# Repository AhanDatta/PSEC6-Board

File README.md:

# PSEC6 Board
PCBs for the Kria K26-based test setup for PSEC6.

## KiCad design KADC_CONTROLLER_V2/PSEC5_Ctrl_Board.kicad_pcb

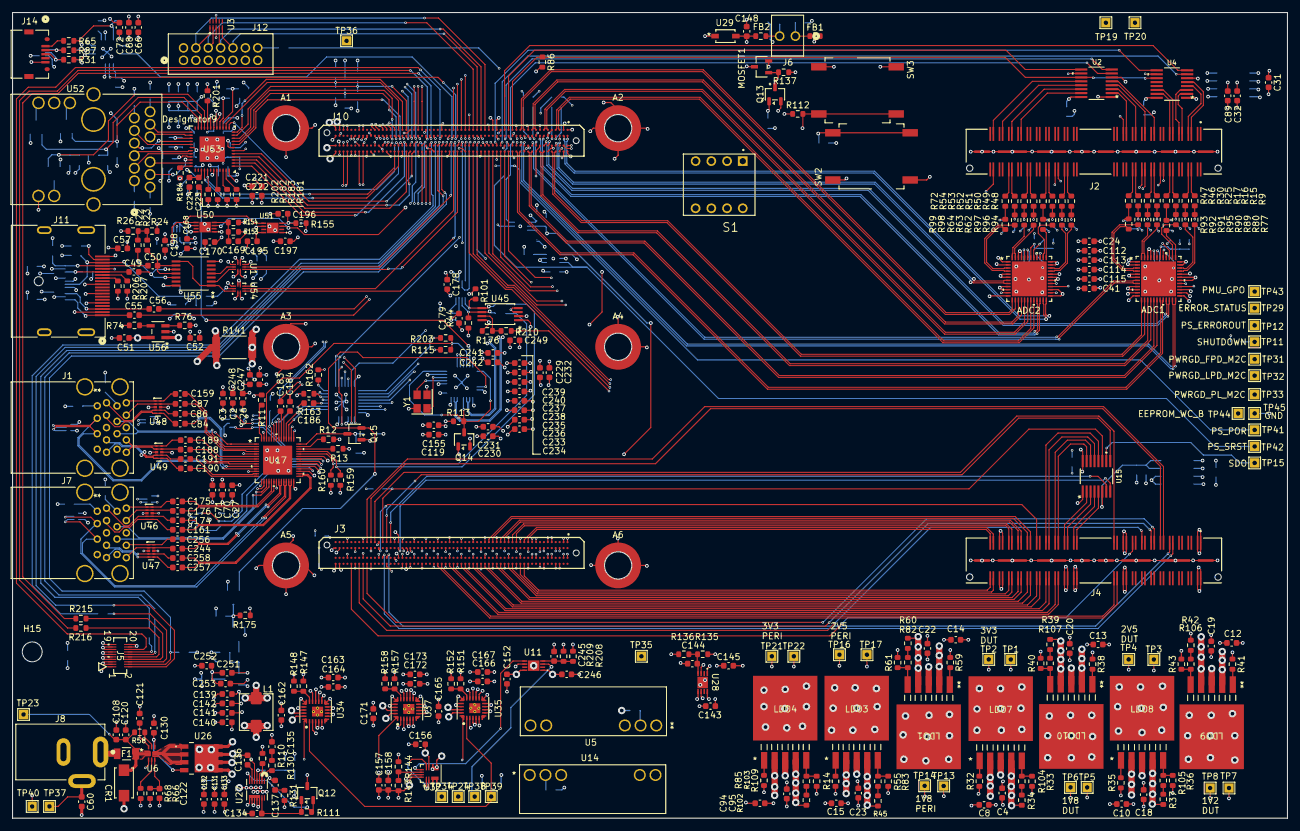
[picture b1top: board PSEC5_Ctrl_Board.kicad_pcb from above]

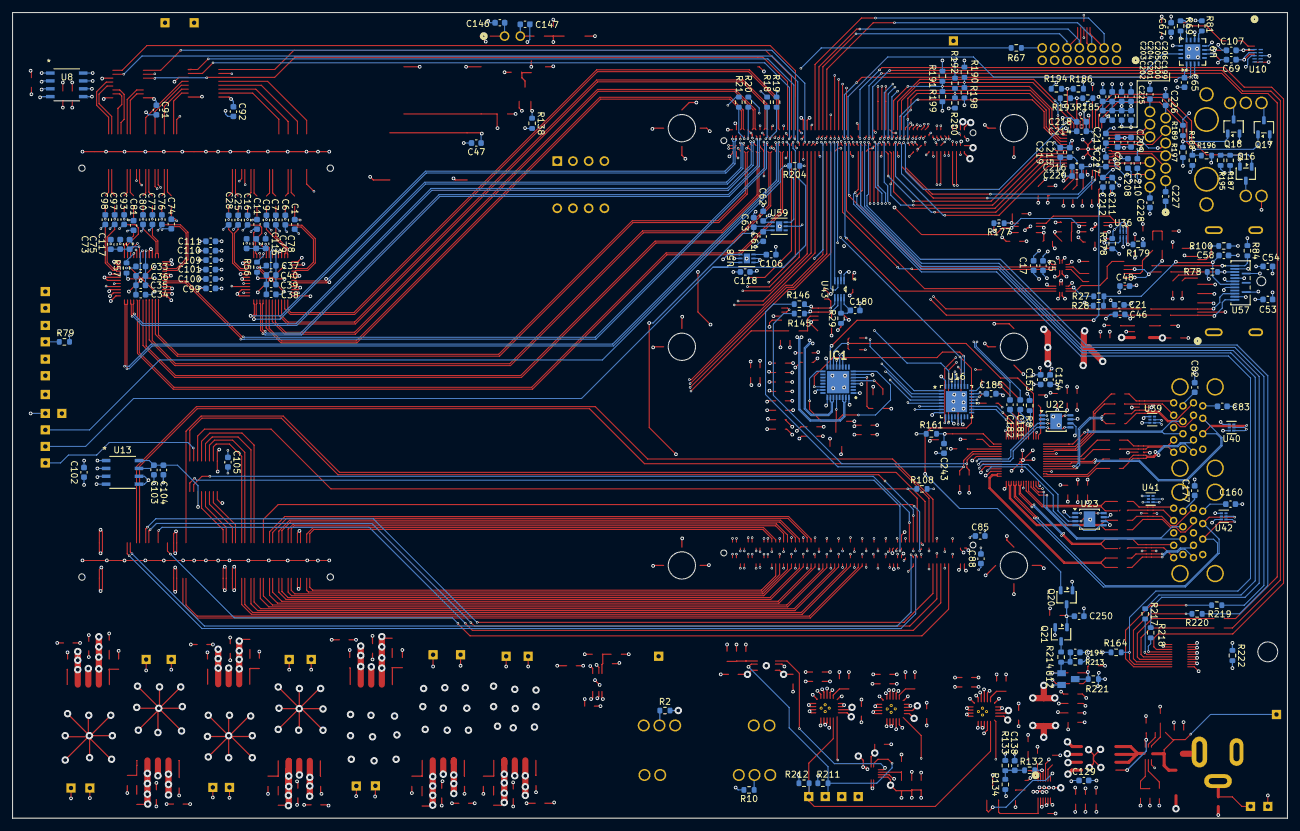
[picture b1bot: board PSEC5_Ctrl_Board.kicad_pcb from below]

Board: 10 copper layers, 206.0 x 130.2 mm, 544 parts (186 on the bottom side), 463 nets.

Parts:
A1, A2, A5, A6: 9774050960R; A_Wurth_WA-SMST_9774050960R_GND_ROUTE_FIX
A3, A4: DNP; A_Wurth_WA-SMST_9774050960R_GND_ROUTE_FIX
ADC1, ADC2: AD9228ABCPZ-65; CP_48_8_ADI
C1, C6, C7, C9, C11, C16, C25, C28, C74, C76, C77, C80, C81, C93, C97, C98, C122: 39p; C_0603_1608Metric
C2, C3, C27, C70, C71, C131, C132, C139, C140, C141, C142, C156, C157, C158, C162, C163, C164, C165, C166, C167, C171, C172, C173: 22u; C_0603_1608Metric
C4, C8, C10, C12, C13, C14, C15, C18, C19, C20, C22, C23, C82, C83, C94, C95, C108, C129, C143, C145, C152, C160, C168, C170, C177, C195, C197, C206, C211, C222, C246, C252: 10u; C_0603_1608Metric
C5, C17, C21, C24, C26, C31, C33, C34, C36, C37, C38, C40, C41, C46, C48, C49, C50, C51, C53, C54, C55, C56, C60, C75, C79, C84, C86, C87, C91, C92, C99, C100, C101, C102, C104, C105, C109, C110, C111, C112, C113, C114, C115, C119, C133, C135, C159, C161, C174, C175, C176, C178, C179, C181, C182, C183, C184, C185, C198, C199, C200, C201, C207, C208, C213, C214, C215, C216, C225, C226, C227, C228, C230, C232, C234, C236, C238, C240, C242, C248, C249, C253: 0.1u; C_0603_1608Metric
C32, C103: 1n; C_0603_1608Metric
C35, C39, C186: 2.2u; C_0603_1608Metric
C47, C61, C62, C65, C67, C72, C85, C88, C106, C118: 100n; C_0603_1608Metric
C52, C153, C154: 47u; C_0603_1608Metric
C57, C58: 10p; C_0603_1608Metric
C63: 10n; C_0603_1608Metric
C66, C68: 4.7u; C_0603_1608Metric
C69, C107: 47p; C_0603_1608Metric
C73, C78: 0.02u; C_0603_1608Metric
C89, C121, C130, C137, C146, C147: DNP; C_0603_1608Metric
C116, C117, C120, C134, C148, C155, C203, C204, C205, C209, C210, C217, C218, C219, C220, C229, C231, C233, C235, C237, C239, C241, C247: 1u; C_0603_1608Metric
C136: 22n; C_0603_1608Metric
C138: 56p; C_0603_1608Metric
C144, C169, C196, C245: 1000p; C_0603_1608Metric
C180: 100p; C_0603_1608Metric
C188, C189, C190, C191, C244, C256, C257, C258: 0.33u; C_0603_1608Metric
C194, C251: 0.47u; C_0603_1608Metric
C202, C212, C221: 0.01u; C_0603_1608Metric
C223, C224: 27p; C_0603_1608Metric
C243, C250: 22p; C_0603_1608Metric
CR1: SMAJ16A; DO214AC_LTF
F1: 0407004.WR; FUSE_407_LTF
FB1, FB2: 600R; R_0603_1608Metric
H15: MountingHole; MountingHole_3.2mm_M3_DIN965
IC1: SI5332BD08940-GM1; QFN50P500X500X90-33N-D
J1, J7: GSB311231HR; GSB311231HR_AMP
J2, J4: QSH-040-01-X-D-DP-A; SAMTEC_QSH-040-01-X-D-DP-A
J3: ADM6-60-01.5-L-4-2-A-TR_BOTTOM; SAMTEC_ADM6-60-01.5-L-4-2-A-TR
J5: DF40C-20DP-0.4V51; CONN20_6p6X2p9_hdr_HIR
J6: 22112022; CONN_A-6373-02A_MOL
J8: PJ-202BH; CUI_PJ-202BH
J10: ADM6-60-01.5-L-4-2-A-TR; SAMTEC_ADM6-60-01.5-L-4-2-A-TR
J11: 472720001; CONN_47272-0001_MOL_Shield_Fixed
J12: 878311420; CONN_87831-1420_MOL
J14: ZX62D-B-5P830; ZX62D-B-5P830_HIR
L1: 1.2u; L_Bourns_SRP5030T
LDO1, LDO3, LDO4, LDO7, LDO8, LDO9, LDO10: LP38501TS-ADJ/NOPB; TS5B
MOSFET1: NDS331N; SOT23_527AG_ONS
Q12, Q13, Q14, Q15, Q16, Q17, Q18, Q20, Q21: BSS806NEH6327XTSA1; SOT-23-3
R2: 4.42k; R_0603_1608Metric
R8, R67, R100, R130, R210, R221: 0R; R_0603_1608Metric
R9, R15, R16, R17, R25, R30, R46, R47, R48, R49, R50, R51, R52, R53, R54, R72: 33.2R; R_0603_1608Metric
R10, R44, R101, R201, R202: 2.21k; R_0603_1608Metric
R11: 12k; R_0603_1608Metric
R12, R13, R29, R157: 200k; R_0603_1608Metric
R14, R32, R33, R35, R36, R38, R40, R41, R43, R56, R57, R59, R61, R69, R74, R76, R79, R81, R83, R85, R109, R112, R136, R137, R138, R153, R154, R161, R163, R175, R177, R192, R204, R213: 10k; R_0603_1608Metric
R18, R19, R20, R21, R82, R86, R107, R108: 4.99k; R_0603_1608Metric
R22, R23: 49.9R; R_0603_1608Metric
R24: 1.5k; R_0603_1608Metric
R26, R198, R200: 2.49k; R_0603_1608Metric
R27, R62, R63, R64, R77, R80, R89, R90, R91, R92, R93, R94, R95, R96, R97, R98, R99: 10R; R_0603_1608Metric
R28, R78, R84, R110, R111, R147, R148, R151, R178, R179, R211, R212: 100k; R_0603_1608Metric
R31, R87: 27R; R_0603_1608Metric
R34, R102: 34k; R_0603_1608Metric
R37, R45, R133: 20k; R_0603_1608Metric
R39, R60: 14.7k; R_0603_1608Metric
R42: 6.8k; R_0603_1608Metric
R55, R105: 11.3k; R_0603_1608Metric
R58: 300k; R_0603_1608Metric
R65, R113, R164, R181, R182, R183: 4.7k; R_0603_1608Metric
R66: 274k; R_0603_1608Metric
R68: 422R; R_0603_1608Metric
R103, R104: 10.5k; R_0603_1608Metric
R106: 3.01k; R_0603_1608Metric
R115, R131, R145, R146, R159, R160, R185, R186, R187, R188, R189, R191, R193, R194, R195, R196, R197, R199, R203, R222: DNP; R_0603_1608Metric
R132, R176, R214: 1k; R_0603_1608Metric
R134: 2.7k; R_0603_1608Metric
R135: 56.2k; R_0603_1608Metric
R141: 0R; RES_HCJ2512_STP
R143: 80k; R_0603_1608Metric
R144: 25k; R_0603_1608Metric
R152: 49.9k; R_0603_1608Metric
R155: 40.2k; R_0603_1608Metric
R158: 44,2k; R_0603_1608Metric
R162: 8.06k; R_0603_1608Metric
R184: 11k; R_0603_1608Metric
R190: 5.76k; R_0603_1608Metric
R206, R207: 1M; R_0603_1608Metric
R208: 26.1k; R_0603_1608Metric
R209: 10.0k; R_0603_1608Metric
R215, R216, R217, R218, R219, R220: 30R; R_0603_1608Metric
S1: DS01C-254-S-04BE; SW_DS01C-254-S-04BE
SW2, SW3: SW_MEC_5G; SW_MEC_5GSH9
TP1, TP3, TP5, TP7, TP13, TP17, TP22, TP40: GND; TestPoint_THTPad_1.5x1.5mm_Drill0.7mm
TP2: 3V3_DUT; TestPoint_THTPad_1.5x1.5mm_Drill0.7mm
TP4: 2V5_DUT; TestPoint_THTPad_1.5x1.5mm_Drill0.7mm
TP6: 1V8_DUT; TestPoint_THTPad_1.5x1.5mm_Drill0.7mm
TP8: 1V2_DUT; TestPoint_THTPad_1.5x1.5mm_Drill0.7mm
TP11: SHUTDOWN; TestPoint_THTPad_1.5x1.5mm_Drill0.7mm
TP12: PS_ERROR_OUT_M2C; TestPoint_THTPad_1.5x1.5mm_Drill0.7mm
TP14: 1V8_PERI; TestPoint_THTPad_1.5x1.5mm_Drill0.7mm
TP15, TP20: SDO2; TestPoint_THTPad_1.5x1.5mm_Drill0.7mm
TP16: 2V5_PERI; TestPoint_THTPad_1.5x1.5mm_Drill0.7mm
TP19: SDO1; TestPoint_THTPad_1.5x1.5mm_Drill0.7mm
TP21: 1V8_Bank; TestPoint_THTPad_1.5x1.5mm_Drill0.7mm
TP23: 12V_Jack; TestPoint_THTPad_1.5x1.5mm_Drill0.7mm
TP24: 12V_IN; TestPoint_THTPad_1.5x1.5mm_Drill0.7mm
TP29: PS_ERROR_STATUS_M2C; TestPoint_THTPad_1.5x1.5mm_Drill0.7mm
TP31: PWRGD_FPD_M2C; TestPoint_THTPad_1.5x1.5mm_Drill0.7mm
TP32: PWRGD_LPD_M2C; TestPoint_THTPad_1.5x1.5mm_Drill0.7mm
TP33: PWRGD_PL_M2C; TestPoint_THTPad_1.5x1.5mm_Drill0.7mm
TP34: 5V0_IN; TestPoint_THTPad_1.5x1.5mm_Drill0.7mm
TP35: UTIL_3V3; TestPoint_THTPad_1.5x1.5mm_Drill0.7mm
TP36: 5V0_SOM; TestPoint_THTPad_1.5x1.5mm_Drill0.7mm
TP37: PWROFF_C2M_B; TestPoint_THTPad_1.5x1.5mm_Drill0.7mm
TP38: CC_PL_PGOOD; TestPoint_THTPad_1.5x1.5mm_Drill0.7mm
TP39: CC_PS_PGOOD; TestPoint_THTPad_1.5x1.5mm_Drill0.7mm
TP41: PS_POR; TestPoint_THTPad_1.5x1.5mm_Drill0.7mm
TP42: PS_SRST; TestPoint_THTPad_1.5x1.5mm_Drill0.7mm
TP43: MIO35_PMU_GPO; TestPoint_THTPad_1.5x1.5mm_Drill0.7mm
TP44: EEPROM_WC_B; TestPoint_THTPad_1.5x1.5mm_Drill0.7mm
TP45: EEPROM_GND; TestPoint_THTPad_1.5x1.5mm_Drill0.7mm
U1, U54: SN74AVC2T245RSWR; RSW0010A
U2, U4, U15: LTC2600CGN_PBF; SSOP-16_GN
U3, U10: PUSB3FR4Z; U_PUSB3FR4Z_NEX
U5, U14: OKX-T/5-D12N-C; OKX-T&slash_5-D12N-C_MUR
U6: MP5016HGQH-Z; QFN-10_MP5016H_MNP_zone_fixed
U8, U13: MCP1501-25E/SN; SOIC8_NARROW_SN_MCH
U9: FT230XQ-R; QFN-16_FTD
U11, U28, U50, U51: MP8904DD-LF-Z; QFN8_MNP
U12: FDN336P; SOT23-3_527AG_FAS
U16: USB3320C-EZK-TR; QFN32_5X5MC_MCH
U17: USB5744/2G; VQFN56_2G_MCH
U22, U23: MP62341DH-LF-Z; MP62341DH-LF-Z_MSOP8E
U26: CSD18532Q5B; CSD18532Q5B_DNK8_zone_fixed
U27: MP8772GQ-Z; QFN-16_MP8772GQ_MNP_GND_fixed
U29: MMSD4148T1G; SOD-123_ONS
U32: MPM3810AGQB-AEC1-Z; MPM3810AGQB-AEC1_Route_Fixed
U34, U35, U37: TPSM82866AA0SRDJR; TPSM82866AA0SRDJR_RDJ0023A_route_fixed
U36: NC7WZ07L6X; MICROPAK6_1X1P45_ONS
U39, U40, U41, U42: TPD4S012DRYR; DRY6
U43: PCA9306DCUR; DCU8
U45: M24C64-DRDW8TP/K; TSSOP8_4P5X3P1X0P65_STM
U46, U47, U48, U49: TPD4E05U06DQAR; DQA0010A
U52: L829-1J1T-43; L829-1J1T-43_BEL
U53: DP83867CRRGZR; RGZ0048B_NV
U55: FIN1019MTCX; TSSOP14_4P4X5_ONS
U56: STMPS2151STR; SOT23-5L_STM
U57: TPD8S009DSMR; DSM15_X
U58, U59: TPS3808G01QDRVRQ1; DRV6_1P6X1
Y1: ABM8AIG-27.000MHZ-12-2Z-T3; Crystal_SMD_Abracon_ABM8AIG-4Pin_3.2x2.5mm

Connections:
1V2_DUT: C19.1, J4.01, J4.02, J4.03, J4.04, LDO9.4 (OUT), R42.1, TP8.1 (1_1)
1V8_DUT: C20.1, J4.42, J4.44, J4.46, J4.48, LDO10.4 (OUT), R39.1, TP6.1 (1_1)
1V8_PERI: ADC1.1 (AVDD), ADC1.2 (AVDD), ADC1.5 (AVDD), ADC1.6 (AVDD), ADC1.9 (AVDD), ADC1.10 (AVDD), ADC1.12 (DRVDD), ADC1.25 (DRVDD), ADC1.27 (AVDD), ADC1.32 (AVDD), ADC1.35 (AVDD), ADC1.36 (AVDD), ADC1.39 (AVDD), ADC1.45 (AVDD), ADC1.46 (AVDD), ADC2.1 (AVDD), ADC2.2 (AVDD), ADC2.5 (AVDD), ADC2.6 (AVDD), ADC2.9 (AVDD), ADC2.10 (AVDD), ADC2.12 (DRVDD), ADC2.25 (DRVDD), ADC2.27 (AVDD), ADC2.32 (AVDD), ADC2.35 (AVDD), ADC2.36 (AVDD), ADC2.39 (AVDD), ADC2.45 (AVDD), ADC2.46 (AVDD), C22.1, C24.1, C41.1, C99.1, C100.1, C101.1, C109.1, C110.1, C111.1, C112.1, C113.1, C114.1, C115.1, LDO1.4 (OUT), R60.1, TP14.1 (1_1)
2V5_DUT: C18.1, J4.33, J4.34, J4.35, J4.36, LDO8.4 (OUT), R37.1, TP4.1 (1_1)
2V5_PERI: C23.1, C91.1, C92.1, C105.1, LDO3.4 (OUT), R45.1, TP16.1 (1_1), U2.16 (VCC), U4.16 (VCC), U15.16 (VCC)
3V3_DUT: C4.1, J4.73, J4.74, J4.75, J4.76, LDO7.4 (OUT), R34.1, TP2.1 (1_1)
3V3_PERI: C31.1, C95.1, C102.1, LDO4.4 (OUT), R102.1, TP21.1 (1_1), U8.1 (VDD), U8.3 (*SHDN), U13.1 (VDD), U13.3 (*SHDN)
5V0_IN: C2.1, C3.1, C26.1, C27.1, C62.1, C70.1, C71.1, C138.2, C139.2, C140.2, C141.2, C142.2, C143.1, C152.2, C156.2, C162.2, C165.2, C171.2, C185.2, C198.2, L1.2, R133.1, R141.1, R163.1, R178.1, R211.1, R212.1, TP34.1 (1_1), U11.8 (IN), U16.21 (VBAT), U22.2 (IN), U23.2 (IN), U28.5 (EN), U28.8 (IN), U32.7 (VIN), U34.3 (VSET_MODE), U34.21 (VIN), U34.22 (VIN), U35.3 (VSET_MODE), U35.21 (VIN), U35.22 (VIN), U36.5 (VCC), U37.3 (VSET_MODE), U37.21 (VIN), U37.22 (VIN), U59.1 (VDD)
5V0_SOM: C153.2, C154.2, C247.2, C248.2, J10.A59 (VCC_SOM), J10.A60 (VCC_SOM), J10.B60 (VCC_SOM), J10.C59 (VCC_SOM), J10.C60 (VCC_SOM), J10.D60 (VCC_SOM), R141.2, TP36.1 (1_1)
12V_IN: C129.1, C131.1, C132.1, C133.1, C148.1, FB1.2, R110.2, TP24.1 (1_1), U5.4 (+VIN), U14.4 (+VIN), U26.5 (D), U26.6 (D), U26.7 (D), U26.8 (D), U27.8 (VIN), U29.1 (CATHODE)
/SOM240_1(1.5)/ADC1_SCLK/DTP: ADC1.28 (SCLK/DTP), J10.B11 (HPA11_N), R19.2
/SOM240_1(1.5)/ADC1_SDIO/ODM: ADC1.29 (SDIO/ODM), J10.B10 (HPA11_P), R18.2
/SOM240_1(1.5)/ADC2_SCLK/DTP: ADC2.28 (SCLK/DTP), J10.B05 (HPA04_N), R20.2
/SOM240_1(1.5)/ADC2_SDIO/ODM: ADC2.29 (SDIO/ODM), J10.B04 (HPA04_P), R21.2
/SOM240_1(1.5)/ADC_CLK1+: ADC1.8 (CLK+), J10.C10 (HPA08_N)
/SOM240_1(1.5)/ADC_CLK1-: ADC1.7 (CLK), J10.C09 (HPA08_P)
/SOM240_1(1.5)/ADC_CLK2+: ADC2.8 (CLK+), J10.C04 (HPA00_CC_N)
/SOM240_1(1.5)/ADC_CLK2-: ADC2.7 (CLK), J10.C03 (HPA00_CC_P)
/SOM240_1(1.5)/ADC_DOUT1+: ADC1.20 (D_+_A), J10.D14 (HPA14_N)
/SOM240_1(1.5)/ADC_DOUT1-: ADC1.19 (D_-_A), J10.D13 (HPA14_P)
/SOM240_1(1.5)/ADC_DOUT2+: ADC1.18 (D_+_B), J10.D11 (HPA09_N)
/SOM240_1(1.5)/ADC_DOUT2-: ADC1.17 (D_-_B), J10.D10 (HPA09_P)
/SOM240_1(1.5)/ADC_DOUT3+: ADC1.16 (D_+_C), J10.D08 (HPA01_N)
/SOM240_1(1.5)/ADC_DOUT3-: ADC1.15 (D_-_C), J10.D07 (HPA01_P)
/SOM240_1(1.5)/ADC_DOUT4+: ADC1.14 (D_+_D), J10.D05 (HPA02_N)
/SOM240_1(1.5)/ADC_DOUT4-: ADC1.13 (D_-_D), J10.D04 (HPA02_P)
/SOM240_1(1.5)/ADC_DOUT5+: ADC2.20 (D_+_A), J10.A03 (HPA06_P)
/SOM240_1(1.5)/ADC_DOUT5-: ADC2.19 (D_-_A), J10.A04 (HPA06_N)
/SOM240_1(1.5)/ADC_DOUT6+: ADC2.18 (D_+_B), J10.A06 (HPA_CLK0_P)
/SOM240_1(1.5)/ADC_DOUT6-: ADC2.17 (D_-_B), J10.A07 (HPA_CLK0_N)
/SOM240_1(1.5)/ADC_DOUT7+: ADC2.16 (D_+_C), J10.A09 (HPA12_P)
/SOM240_1(1.5)/ADC_DOUT7-: ADC2.15 (D_-_C), J10.A10 (HPA12_N)
/SOM240_1(1.5)/ADC_DOUT8+: ADC2.14 (D_+_D), J10.A12 (HPA13_P)
/SOM240_1(1.5)/ADC_DOUT8-: ADC2.13 (D_-_D), J10.A13 (HPA13_N)
/SOM240_1(1.5)/CLR_DAC*: J10.A15 (HDA09), R86.1, U2.11 (*CLR), U4.11 (*CLR)
/SOM240_1(1.5)/CS/LD_DAC1*: J10.B16 (HDA03), U2.7 (*CS/LD)
/SOM240_1(1.5)/CS/LD_DAC2*: J10.C18 (HDA06), U4.7 (*CS/LD)
/SOM240_1(1.5)/DataClk1+: ADC1.24 (DCO+), J10.C12 (HPA10_CC_P)
/SOM240_1(1.5)/DataClk1-: ADC1.23 (DCO-), J10.C13 (HPA10_CC_N)
/SOM240_1(1.5)/DataClk2+: ADC2.24 (DCO+), J10.B01 (HPA05_CC_P)
/SOM240_1(1.5)/DataClk2-: ADC2.23 (DCO-), J10.B02 (HPA05_CC_N)
/SOM240_1(1.5)/DisplayPort/DP_AUX_C_N: C50.2, J11.17, R84.1, U57.1 (D0+)
/SOM240_1(1.5)/DisplayPort/DP_AUX_C_P: C49.2, J11.15, R78.2, U57.3 (D0-)
/SOM240_1(1.5)/DisplayPort/DP_HPD_R: C58.1, J11.18, R27.2, R28.2, U57.7 (D2+)
/SOM240_1(1.5)/DisplayPort/DP_LN0_C_N: C56.1, J11.3, U57.10 (D3+)
/SOM240_1(1.5)/DisplayPort/DP_LN0_C_P: C55.1, J11.1, U57.12 (D3-)
/SOM240_1(1.5)/FWUEN_B: C47.1, J10.C28 (MIO12_FWUEN_C2M_L), SW2.3 (B), SW2.4 (B)
/SOM240_1(1.5)/FrameClk1+: ADC1.22 (FCO+), J10.C07 (HPA03_N)
/SOM240_1(1.5)/FrameClk1-: ADC1.21 (FCO-), J10.C06 (HPA03_P)
/SOM240_1(1.5)/FrameClk2+: ADC2.22 (FCO+), J10.B08 (HPA07_N)
/SOM240_1(1.5)/FrameClk2-: ADC2.21 (FCO-), J10.B07 (HPA07_P)
/SOM240_1(1.5)/GEM3_MDC: J10.D44 (MIO76), U53.16 (MDC)
/SOM240_1(1.5)/GEM3_MDIO: J10.D45 (MIO77), R202.2, U53.17 (MDIO)
/SOM240_1(1.5)/GTR_DP1_M2C_N: C56.2, J10.A48 (GTR_DP1_M2C_N)
/SOM240_1(1.5)/GTR_DP1_M2C_P: C55.2, J10.A47 (GTR_DP1_M2C_P)
/SOM240_1(1.5)/JTAG_CLK: J10.A25 (JTAG_TCK_C2M), J12.6, U3.2 (CH2)
/SOM240_1(1.5)/JTAG_TDI: J10.A24 (JTAG_TDI_C2M), J12.10, U3.5 (CH4)
/SOM240_1(1.5)/JTAG_TDO: J10.A23 (JTAG_TDO_M2C), J12.8, U3.4 (CH3)
/SOM240_1(1.5)/JTAG_TMS: J10.A22 (JTAG_TMS_C2M), J12.4, U3.1 (CH1)
/SOM240_1(1.5)/MIO27: J10.D29 (MIO27), U1.8 (A1)
/SOM240_1(1.5)/MIO28: J10.D30 (MIO28), U54.9 (A2)
/SOM240_1(1.5)/MIO29: J10.C30 (MIO29), U54.8 (A1)
/SOM240_1(1.5)/MIO30: J10.C31 (MIO30), U1.9 (A2)
/SOM240_1(1.5)/MODE0: J10.A27 (MODE0_C2M), S1.1A
/SOM240_1(1.5)/MODE1: J10.A28 (MODE1_C2M), S1.2A
/SOM240_1(1.5)/MODE2: J10.A29 (MODE2_C2M), S1.3A
/SOM240_1(1.5)/MODE3: J10.A30 (MODE3_C2M), S1.4A
/SOM240_1(1.5)/Peripherals_Ctrl1/READOUT1+: ADC1.33 (VIN_+_A), R77.2
/SOM240_1(1.5)/Peripherals_Ctrl1/READOUT1-: ADC1.34 (VIN__A), R80.2
/SOM240_1(1.5)/Peripherals_Ctrl1/READOUT2+: ADC1.38 (VIN+B), R89.2
/SOM240_1(1.5)/Peripherals_Ctrl1/READOUT2-: ADC1.37 (VIN-B), R90.2
/SOM240_1(1.5)/Peripherals_Ctrl1/READOUT3+: ADC1.47 (VIN+C), R95.2
/SOM240_1(1.5)/Peripherals_Ctrl1/READOUT3-: ADC1.48 (VIN-C), R91.2
/SOM240_1(1.5)/Peripherals_Ctrl1/READOUT4+: ADC1.4 (VIN_+_D), R92.2
/SOM240_1(1.5)/Peripherals_Ctrl1/READOUT4-: ADC1.3 (VIN__D), R93.2
/SOM240_1(1.5)/Peripherals_Ctrl1/READOUT5+: ADC2.33 (VIN_+_A), R94.2
/SOM240_1(1.5)/Peripherals_Ctrl1/READOUT5-: ADC2.34 (VIN__A), R96.2
/SOM240_1(1.5)/Peripherals_Ctrl1/READOUT6+: ADC2.38 (VIN+B), R97.2
/SOM240_1(1.5)/Peripherals_Ctrl1/READOUT6-: ADC2.37 (VIN-B), R62.2
/SOM240_1(1.5)/Peripherals_Ctrl1/READOUT7+: ADC2.47 (VIN+C), R63.2
/SOM240_1(1.5)/Peripherals_Ctrl1/READOUT7-: ADC2.48 (VIN-C), R64.2
/SOM240_1(1.5)/Peripherals_Ctrl1/READOUT8+: ADC2.4 (VIN_+_D), R98.2
/SOM240_1(1.5)/Peripherals_Ctrl1/READOUT8-: ADC2.3 (VIN__D), R99.2
/SOM240_1(1.5)/RGMII_RX_CLK: J10.B44 (MIO70), U53.32 (RX_CLK)
/SOM240_1(1.5)/RGMII_RX_CTL: J10.A44 (MIO75), R190.2, R198.1, U53.38 (RX_DV_RX_CTRL)
/SOM240_1(1.5)/RGMII_RX_D0: J10.B45 (MIO71), R192.2, R200.1, U53.33 (RX_D0)
/SOM240_1(1.5)/RGMII_RX_D1: J10.B46 (MIO72), U53.34 (RX_D1)
/SOM240_1(1.5)/RGMII_RX_D2: J10.A42 (MIO73), R191.2, R199.1, U53.35 (RX_D2)
/SOM240_1(1.5)/RGMII_RX_D3: J10.A43 (MIO74), U53.36 (RX_D3)
/SOM240_1(1.5)/RGMII_TX_CLK: J10.D40 (MIO64), U53.29 (GTX_CLK)
/SOM240_1(1.5)/RGMII_TX_CTL: J10.C44 (MIO69), U53.37 (TX_EN_TX_CTRL)
/SOM240_1(1.5)/RGMII_TX_D0: J10.D41 (MIO65), U53.28 (TX_D0)
/SOM240_1(1.5)/RGMII_TX_D1: J10.D42 (MIO66), U53.27 (TX_D1)
/SOM240_1(1.5)/RGMII_TX_D2: J10.C42 (MIO67), U53.26 (TX_D2)
/SOM240_1(1.5)/RGMII_TX_D3: J10.C43 (MIO68), U53.25 (TX_D3)
/SOM240_1(1.5)/SCK_DAC1: J10.B17 (HDA04), U2.8 (SCK)
/SOM240_1(1.5)/SCK_DAC2: J10.A17 (HDA11), U4.8 (SCK)
/SOM240_1(1.5)/SDI_DAC_BIAS: J10.C19 (HDA07), U4.9 (SDI)
/SOM240_1(1.5)/SDI_DAC_THRES: J10.A16 (HDA10), U2.9 (SDI)
/SOM240_1(1.5)/SD_CLK: J10.B37 (MIO51), R216.1
/SOM240_1(1.5)/SD_CMD: J10.B36 (MIO50), R215.1
/SOM240_1(1.5)/SD_DAT0: J10.D34 (MIO46), R217.1
/SOM240_1(1.5)/SD_DAT1: J10.C34 (MIO47), R218.1
/SOM240_1(1.5)/SD_DAT2: J10.C35 (MIO48), R219.1
/SOM240_1(1.5)/SD_DAT3: J10.C36 (MIO49), R220.1
/SOM240_1(1.5)/SD_DETECT: J5.4, J10.D33 (MIO45), R164.2
/SOM240_1(1.5)/SD_SEL: J5.16, J10.B33 (MIO39)
/SOM240_1(1.5)/SHUTDOWN: J10.C32 (MIO31_PMU_GPI), R79.2, TP11.1 (1_1)
/SOM240_1(1.5)/UART_RXD: J10.B29 (MIO36), U9.2 (RXD)
/SOM240_1(1.5)/UART_TXD: J10.B30 (MIO37), U9.15 (TXD)
/SOM240_1(1.5)/USB0_CLK: J10.D36 (MIO52), U16.1 (CLKOUT)
/SOM240_1(1.5)/USB0_DATA0: J10.C39 (MIO56), U16.3 (DATA0)
/SOM240_1(1.5)/USB0_DATA1: J10.C40 (MIO57), U16.4 (DATA1)
/SOM240_1(1.5)/USB0_DATA2: J10.D38 (MIO54), U16.5 (DATA2)
/SOM240_1(1.5)/USB0_DATA3: J10.B41 (MIO59), U16.6 (DATA3)
/SOM240_1(1.5)/USB0_DATA4: J10.B42 (MIO60), U16.7 (DATA4)
/SOM240_1(1.5)/USB0_DATA5: J10.A38 (MIO61), U16.9 (DATA5)
/SOM240_1(1.5)/USB0_DATA6: J10.A39 (MIO62), U16.10 (DATA6)
/SOM240_1(1.5)/USB0_DATA7: J10.A40 (MIO63), U16.13 (DATA7)
/SOM240_1(1.5)/USB0_DIR: J10.D37 (MIO53), U16.31 (DIR)
/SOM240_1(1.5)/USB0_NXT: J10.C38 (MIO55), U16.2 (NXT)
/SOM240_1(1.5)/USB0_STP: J10.B40 (MIO58), U16.29 (STP)
/SOM240_1(1.5)/USB-UART1/UART_VSENSE: R65.1, R69.2, U9.12 (CBUS0)
/SOM240_1(1.5)/USB-UART1/USB3320_D_N: U16.19 (DM), U17.46 (USB2UP_DM)
/SOM240_1(1.5)/USB-UART1/USB3320_D_P: U16.18 (DP), U17.45 (USB2UP_DP)
/SOM240_1(1.5)/USB-UART1/USB_C_SSTX1+: C159.1, J1.18 (SSTX+), U48.1 (D1+), U48.10 (NC)
/SOM240_1(1.5)/USB-UART1/USB_C_SSTX1-: C87.1, J1.17 (SSTX-), U48.2 (D1-), U48.9 (NC)
/SOM240_1(1.5)/USB-UART1/USB_C_SSTX2+: C86.2, J1.9 (SSTX+), U48.4 (D2+), U48.7 (NC)
/SOM240_1(1.5)/USB-UART1/USB_C_SSTX2-: C84.2, J1.8 (SSTX-), U48.5 (D2-), U48.6 (NC)
/SOM240_1(1.5)/USB-UART1/USB_C_SSTX3+: C175.1, J7.18 (SSTX+), U46.1 (D1+), U46.10 (NC)
/SOM240_1(1.5)/USB-UART1/USB_C_SSTX3-: C176.1, J7.17 (SSTX-), U46.2 (D1-), U46.9 (NC)
/SOM240_1(1.5)/USB-UART1/USB_C_SSTX4+: C174.2, J7.9 (SSTX+), U46.4 (D2+), U46.7 (NC)
/SOM240_1(1.5)/USB-UART1/USB_C_SSTX4-: C161.2, J7.8 (SSTX-), U46.5 (D2-), U46.6 (NC)
/SOM240_1(1.5)/USB-UART1/USB_D1+: J1.12 (D+), U17.1 (USB2DN_DP1/PRT_DIS_P1), U39.1 (D+)
/SOM240_1(1.5)/USB-UART1/USB_D1-: J1.11 (D-), U17.2 (USB2DN_DM1/PRT_DIS_M1), U39.2 (D-)
/SOM240_1(1.5)/USB-UART1/USB_D2+: J1.3 (D+), U17.8 (USB2DN_DP2/PRT_DIS_P2), U40.1 (D+)
/SOM240_1(1.5)/USB-UART1/USB_D2-: J1.2 (D-), U17.9 (USB2DN_DM2/PRT_DIS_M2), U40.2 (D-)
/SOM240_1(1.5)/USB-UART1/USB_D3+: J7.12 (D+), U17.17 (USB2DN_DP3/PRT_DIS_P3), U41.1 (D+)
/SOM240_1(1.5)/USB-UART1/USB_D3-: J7.11 (D-), U17.18 (USB2DN_DM3/PRT_DIS_M3), U41.2 (D-)
/SOM240_1(1.5)/USB-UART1/USB_D4+: J7.3 (D+), U17.24 (USB2DN_DP4/PRT_DIS_P4), U42.1 (D+)
/SOM240_1(1.5)/USB-UART1/USB_D4-: J7.2 (D-), U17.25 (USB2DN_DM4/PRT_DIS_M4), U42.2 (D-)
/SOM240_1(1.5)/USB-UART1/USB_PRT_CTRL1: U17.36 (PRT_CTL1), U22.3 (EN1), U22.8 (FLAG1_B)
/SOM240_1(1.5)/USB-UART1/USB_PRT_CTRL2: U17.35 (PRT_CTL2), U22.4 (EN2), U22.5 (FLAG2_B)
/SOM240_1(1.5)/USB-UART1/USB_PRT_CTRL3: U17.34 (PRT_CTL3), U23.3 (EN1), U23.8 (FLAG1_B)
/SOM240_1(1.5)/USB-UART1/USB_PRT_CTRL4: U17.32 (PRT_CTL4/GANG_PWR), U23.4 (EN2), U23.5 (FLAG2_B)
/SOM240_1(1.5)/USB-UART1/USB_RESET#: R81.1, U9.9 (RESET#)
/SOM240_1(1.5)/USB-UART1/USB_SSRX1+: C189.2, J1.15 (SSRX+), U49.1 (D1+), U49.10 (NC)
/SOM240_1(1.5)/USB-UART1/USB_SSRX1-: C188.2, J1.14 (SSRX-), U49.2 (D1-), U49.9 (NC)
/SOM240_1(1.5)/USB-UART1/USB_SSRX1_C+: C189.1, U17.6 (USB3DN_RXDP1)
/SOM240_1(1.5)/USB-UART1/USB_SSRX1_C-: C188.1, U17.7 (USB3DN_RXDM1)
/SOM240_1(1.5)/USB-UART1/USB_SSRX2+: C191.2, J1.6 (SSRX+), U49.4 (D2+), U49.7 (NC)
/SOM240_1(1.5)/USB-UART1/USB_SSRX2-: C190.2, J1.5 (SSRX-), U49.5 (D2-), U49.6 (NC)
/SOM240_1(1.5)/USB-UART1/USB_SSRX2_C+: C191.1, U17.13 (USB3DN_RXDP2)
/SOM240_1(1.5)/USB-UART1/USB_SSRX2_C-: C190.1, U17.14 (USB3DN_RXDM2)
/SOM240_1(1.5)/USB-UART1/USB_SSRX3+: C256.2, J7.15 (SSRX+), U47.1 (D1+), U47.10 (NC)
/SOM240_1(1.5)/USB-UART1/USB_SSRX3-: C244.2, J7.14 (SSRX-), U47.2 (D1-), U47.9 (NC)
/SOM240_1(1.5)/USB-UART1/USB_SSRX3_C+: C256.1, U17.22 (USB3DN_RXDP3)
/SOM240_1(1.5)/USB-UART1/USB_SSRX3_C-: C244.1, U17.23 (USB3DN_RXDM3)
/SOM240_1(1.5)/USB-UART1/USB_SSRX4+: C258.2, J7.6 (SSRX+), U47.4 (D2+), U47.7 (NC)
/SOM240_1(1.5)/USB-UART1/USB_SSRX4-: C257.2, J7.5 (SSRX-), U47.5 (D2-), U47.6 (NC)
/SOM240_1(1.5)/USB-UART1/USB_SSRX4_C+: C258.1, U17.29 (USB3DN_RXDP4)
/SOM240_1(1.5)/USB-UART1/USB_SSRX4_C-: C257.1, U17.30 (USB3DN_RXDM4)
/SOM240_1(1.5)/USB-UART1/USB_SSTX1+: C159.2, U17.3 (USB3DN_TXDP1)
/SOM240_1(1.5)/USB-UART1/USB_SSTX1-: C87.2, U17.4 (USB3DN_TXDM1)
/SOM240_1(1.5)/USB-UART1/USB_SSTX2+: C86.1, U17.10 (USB3DN_TXDP2)
/SOM240_1(1.5)/USB-UART1/USB_SSTX2-: C84.1, U17.11 (USB3DN_TXDM2)
/SOM240_1(1.5)/USB-UART1/USB_SSTX3+: C175.2, U17.19 (USB3DN_TXDP3)
/SOM240_1(1.5)/USB-UART1/USB_SSTX3-: C176.2, U17.20 (USB3DN_TXDM3)
/SOM240_1(1.5)/USB-UART1/USB_SSTX4+: C174.1, U17.26 (USB3DN_TXDP4)
/SOM240_1(1.5)/USB-UART1/USB_SSTX4-: C161.1, U17.27 (USB3DN_TXDM4)
/SOM240_1(1.5)/USB-UART1/USB_VBUS1: C82.1, J1.10 (VBUS), U22.7 (OUT1), U39.6 (Vbus)
/SOM240_1(1.5)/USB-UART1/USB_VBUS2: C83.1, J1.1 (VBUS), U22.6 (OUT2), U40.6 (Vbus)
/SOM240_1(1.5)/USB-UART1/USB_VBUS3: C177.1, J7.10 (VBUS), U23.7 (OUT1), U41.6 (Vbus)
/SOM240_1(1.5)/USB-UART1/USB_VBUS4: C160.1, J7.1 (VBUS), U23.6 (OUT2), U42.6 (Vbus)
/SOM240_1(1.5)/ethernet1/GEM_GPIO0: R186.2, R194.1, U53.39 (GPIO_0)
/SOM240_1(1.5)/ethernet1/GEM_GPIO1: R185.2, R193.1, U53.40 (GPIO_1)
/SOM240_1(1.5)/ethernet1/GEM_LED0: Q18.1 (G), R189.2, R197.1, U53.47 (LED_0)
/SOM240_1(1.5)/ethernet1/GEM_LED0_CA: Q18.3 (D), U52.15 (LEFT_ORG_CA)
/SOM240_1(1.5)/ethernet1/GEM_LED1: Q17.1 (G), R188.2, R196.1, U53.46 (LED_1)
/SOM240_1(1.5)/ethernet1/GEM_LED1_CA: Q17.3 (D), U52.17 (LEFT_GRN_CA)
/SOM240_1(1.5)/ethernet1/GEM_LED2: Q16.1 (G), R187.2, R195.1, U53.45 (LED_2)
/SOM240_1(1.5)/ethernet1/GEM_LED2_CA: Q16.3 (D), U52.13 (RIGHT_YLW_CA)
/SOM240_1(1.5)/ethernet1/GEM_TD_A_N: U52.10 (TD0_N), U53.2 (TD_M_A)
/SOM240_1(1.5)/ethernet1/GEM_TD_A_P: U52.11 (TD0_P), U53.1 (TD_P_A)
/SOM240_1(1.5)/ethernet1/GEM_TD_B_N: U52.5 (TD1_N), U53.5 (TD_M_B)
/SOM240_1(1.5)/ethernet1/GEM_TD_B_P: U52.4 (TD1_P), U53.4 (TD_P_B)
/SOM240_1(1.5)/ethernet1/GEM_TD_C_N: U52.2 (TD2_N), U53.8 (TD_M_C)
/SOM240_1(1.5)/ethernet1/GEM_TD_C_P: U52.3 (TD2_P), U53.7 (TD_P_C)
/SOM240_1(1.5)/ethernet1/GEM_TD_D_N: U52.9 (TD3_N), U53.11 (TD_M_D)
/SOM240_1(1.5)/ethernet1/GEM_TD_D_P: U52.8 (TD3_P), U53.10 (TD_P_D)
/SOM240_2(1.5)/CLR_DAC*_ped: J3.A48 (HDB20), R108.1, U15.11 (*CLR)
/SOM240_2(1.5)/CS/LD_DAC_ped*: J3.A46 (HDB18), U15.7 (*CS/LD)
/SOM240_2(1.5)/SCK_DAC_ped: J3.B44 (HDB12), U15.8 (SCK)
/SOM240_2(1.5)/SDI_DAC_ped: J3.A47 (HDB19), U15.9 (SDI)
/pl_pwr/ETH_REG_EN: R179.2, U36.6 (Y1), U50.5 (EN), U51.5 (EN)
A11: J3.A11 (HPB15_CC_P), J4.79
A12: J3.A12 (HPB15_CC_N), J4.77
A14: J3.A14 (HPB08_P), J4.71
A15: J3.A15 (HPB08_N), J4.69
A17: J3.A17 (HPB12_P), J4.67
A18: J3.A18 (HPB12_N), J4.65
A20: J3.A20 (HPB06_P), J4.63
A21: J3.A21 (HPB06_N), J4.61
ADC_CNV: J3.D56 (HDC03), J4.31
ADC_SCLK: J3.D53 (HDC01), J4.23
ADC_SDI: J3.D52 (HDC00_CC), J4.21
ADC_SDO: J3.D54 (HDC02), J4.27
CC_PL_PGOOD: R211.2, TP38.1 (1_1), U11.3 (PG), U32.8 (PG)
CC_PS_PGOOD: C63.1, Q14.1 (G), R212.2, TP39.1 (1_1), U34.2 (PG), U35.2 (PG), U36.4 (Y2), U50.3 (PG), U51.3 (PG), U59.2 (SENSE)
CP_IBIAS: J2.15, U4.15 (VOUTH)
CSB: J3.C47 (HDB07), J4.15
D12: J3.D12 (HPB01_P), J4.80
D13: J3.D13 (HPB01_N), J4.78
D15: J3.D15 (HPB00_CC_P), J4.72
D16: J3.D16 (HPB00_CC_N), J4.70
D18: J3.D18 (HPB_CLK0_P), J4.68
D19: J3.D19 (HPB_CLK0_N), J4.66
D21: J3.D21 (HPB04_P), J4.64
D22: J3.D22 (HPB04_N), J4.62
D24: J3.D24 (HPB17_P), J4.60
D25: J3.D25 (HPB17_N), J4.58
D27: J3.D27 (HPC09_P), J4.56
D28: J3.D28 (HPC09_N), J4.54
D30: J3.D30 (HPC01_P), J4.52
D31: J3.D31 (HPC01_N), J4.50
D33: J3.D33 (HPC00_CC_P), J4.40
D34: J3.D34 (HPC00_CC_N), J4.38
DAC_SCLK: J3.A51 (HDB22), J4.19
DAC_VREF: C32.1, C89.1, U2.6 (REF), U4.6 (REF), U8.7 (OUT), U8.8 (FEEDBACK)
DAC_V_IN: J3.A50 (HDB21), J4.39
DISCBIAS: J2.09, U4.2 (VOUTA)
DIVIDER_IBIAS: J2.13, U4.14 (VOUTG)
DP_3V3: C52.2, C57.1, J11.20, U56.1 (OUT), U57.6 (D1-)
Disc_Thresh1: J2.33, U2.2 (VOUTA)
Disc_Thresh2: J2.29, U2.3 (VOUTB)
Disc_Thresh3: J2.25, U2.4 (VOUTC)
Disc_Thresh4: J2.21, U2.5 (VOUTD)
Disc_Thresh5: J2.77, U2.12 (VOUTE)
Disc_Thresh6: J2.73, U2.13 (VOUTF)
Disc_Thresh7: J2.69, U2.14 (VOUTG)
Disc_Thresh8: J2.65, U2.15 (VOUTH)
EEPROM_WC_B: R210.1, TP44.1 (1_1)
ETH_1V0: C169.2, C170.2, C213.1, C214.1, C215.1, C216.1, C217.1, C218.1, C219.1, C220.1, C221.1, C222.1, R153.1, U50.1 (OUT), U53.6 (VDD1P0), U53.24 (VDD1P0), U53.31 (VDD1P0), U53.42 (VDD1P0)
ETH_2V5: C196.2, C197.2, C207.1, C208.1, C209.1, C210.1, C211.1, C212.1, R155.1, U51.1 (OUT), U53.3 (VDDA2P5), U53.9 (VDDA2P5)
ETH_REF_CLK: C223.2, IC1.15 (OUT1)
GND: A1.1 (1_1), A2.1 (1_1), A3.1 (1_1), A4.1 (1_1), A5.1 (1_1), A6.1 (1_1), ADC1.11 (DRGND), ADC1.26 (DRGND), ADC1.30 (CSB), ADC1.31 (PDWN), ADC1.41 (SENSE), ADC1.49 (EPAD), ADC2.11 (DRGND), ADC2.26 (DRGND), ADC2.30 (CSB), ADC2.31 (PDWN), ADC2.41 (SENSE), ADC2.49 (EPAD), C1.2, C2.2, C3.2, C4.2, C5.2, C6.2, C7.2, C8.1, C9.2, C10.1, C11.2, C12.1, C13.2, C14.1, C15.1, C16.2, C17.2, C18.2, C19.2, C20.2, C21.2, C22.2, C23.2, C24.2, C25.2, C26.2, C27.2, C28.2, C31.2, C32.2, C33.2, C34.2, C37.2, C38.2, C41.2, C46.2, C47.2, C48.2, C51.1, C52.1, C53.1, C54.1, C57.2, C58.2, C60.2, C61.2, C62.2, C63.2, C65.2, C66.2, C67.2, C68.2, C69.2, C70.2, C71.2, C72.2, C73.2, C74.2, C75.2, C76.2, C77.2, C78.2, C79.2, C80.2, C81.2, C82.2, C83.2, C85.2, C88.2, C89.2, C91.2, C92.2, C93.2, C94.1, C95.2, C97.2, C98.2, C99.2, C100.2, C101.2, C102.2, C103.2, C104.2, C105.2, C106.2, C107.2, C108.2, C109.2, C110.2, C111.2, C112.2, C113.2, C114.2, C115.2, C116.2, C117.2, C118.2, C119.2, C120.2, C121.2, C122.2, C129.2, C130.2, C131.2, C132.2, C133.2, C134.2, C136.2, C139.1, C140.1, C141.1, C142.1, C143.2, C145.2, C146.2, C147.2, C152.1, C153.1, C154.1, C155.2, C156.1, C157.1, C158.1, C160.2, C162.1, C163.1, C164.1, C165.1, C166.1, C167.1, C168.1, C170.1, C171.1, C172.1, C173.1, C177.2, C178.2, C179.2, C180.2, C185.1, C186.2, C195.1, C197.1, C198.1, C199.2, C200.2, C201.2, C202.2, C203.2, C204.2, C205.2, C206.2, C207.2, C208.2, C209.2, C210.2, C211.2, C212.2, C213.2, C214.2, C215.2, C216.2, C217.2, C218.2, C219.2, C220.2, C221.2, C222.2, C224.1, C225.1, C226.1, C227.1, C228.1, C229.2, C230.2, C231.2, C232.2, C233.2, C234.2, C235.2, C236.2, C237.2, C238.2, C239.2, C240.2, C241.2, C242.2, C243.2, C246.1, C247.1, C248.1, C249.2, C250.2, C252.2, C253.2, CR1.2, IC1.33 (GND), J1.4 (GND), J1.7 (GND_DRAIN), J1.13 (GND), J1.16 (GND_DRAIN), J2.G1 (GND_S1), J2.G2 (GND_S1__1), J2.G3 (GND_S1__2), J2.G4 (GND_S1__3), J2.G5 (GND_S2), J2.G6 (GND_S2__1), J2.G7 (GND_S2__2), J2.G8 (GND_S2__3)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
GTR_DP2_C2M_N: C183.1, J10.B54 (GTR_DP2_C2M_N)
GTR_DP2_C2M_P: C184.1, J10.B53 (GTR_DP2_C2M_P)
GTR_DP2_M2C_N: C181.1, J10.D58 (GTR_DP2_M2C_N)
GTR_DP2_M2C_P: C182.1, J10.D57 (GTR_DP2_M2C_P)
GTR_REFCLK0_C2M_N: IC1.30 (OUT5B), J10.C48 (GTR_REFCLK0_C2M_N)
GTR_REFCLK0_C2M_P: IC1.31 (OUT5), J10.C47 (GTR_REFCLK0_C2M_P)
GTR_REFCLK1_C2M_N: IC1.26 (OUT4B), J10.B50 (GTR_REFCLK1_C2M_N)
GTR_REFCLK1_C2M_P: IC1.27 (OUT4), J10.B49 (GTR_REFCLK1_C2M_P)
GTR_REFCLK2_C2M_N: IC1.11 (OUT0B), J10.D54 (GTR_REFCLK2_C2M_N)
GTR_REFCLK2_C2M_P: IC1.12 (OUT0), J10.D53 (GTR_REFCLK2_C2M_P)
HDA20: J10.C24 (HDA20), Q13.1 (G), R138.1
I2C_SCK: J10.C26 (MIO24_I2C_SCK), U43.3 (SCL1)
I2C_SCK_LS: R44.2, R145.1, U43.6 (SCL2), U45.6 (SCL)
I2C_SDA: J10.C27 (MIO25_I2C_SDA), U43.4 (SDA1)
I2C_SDA_LS: R101.2, R146.1, U43.5 (SDA2), U45.5 (SDA)
unnamed: ADC1.40 (RBIAS), R57.1
unnamed: ADC1.43 (REFB), C34.1, C35.2, C36.2
unnamed: ADC1.44 (REFT), C33.1, C35.1, C36.1
unnamed: ADC1.42 (VREF), C73.1, C75.1, C117.1
unnamed: ADC2.40 (RBIAS), R56.1
unnamed: ADC2.43 (REFB), C38.1, C39.2, C40.2
unnamed: ADC2.44 (REFT), C37.1, C39.1, C40.1
unnamed: ADC2.42 (VREF), C78.1, C79.1, C116.1
unnamed: C1.1, R72.2, R99.1
unnamed: C6.1, R54.2, R98.1
unnamed: C7.1, R53.2, R64.1
unnamed: C9.1, R52.2, R63.1
unnamed: C11.1, R51.2, R62.1
unnamed: C16.1, R50.2, R97.1
unnamed: C25.1, R49.2, R96.1
unnamed: C28.1, R48.2, R94.1
unnamed: C74.1, R47.2, R93.1
unnamed: C76.1, R46.2, R92.1
unnamed: C77.1, R30.2, R91.1
unnamed: C80.1, R25.2, R95.1
unnamed: C81.1, R17.2, R90.1
unnamed: C93.1, R16.2, R89.1
unnamed: C97.1, R15.2, R80.1
unnamed: C98.1, R9.2, R77.1
unnamed: C108.1, C120.1, CR1.1, F1.2, R58.2, TP23.1 (1_1), U6.1 (VCC), U6.2 (VCC)
unnamed: C135.1, R130.2
unnamed: C137.1, R131.1
unnamed: C138.1, R132.1, R133.2, R134.1
unnamed: C146.1, FB1.1, J6.1
unnamed: C147.1, FB2.2, J6.2
unnamed: C194.2, C251.1, R213.2, R214.1, U12.1
unnamed: C251.2, C252.1, C253.1, R221.1, U12.3
unnamed: F1.1, J8.1
unnamed: IC1.8 (INPUT1), IC1.17 (INPUT2), IC1.28 (INPUT4), Q14.3 (D), R113.2
unnamed: IC1.5 (XA/CLKIN1), Y1.3
unnamed: IC1.6 (XB), Y1.1
unnamed: J5.2, R219.2
unnamed: J5.6, R220.2
unnamed: J5.8, R215.2
unnamed: J5.10, R216.2
unnamed: J5.12, R217.2
unnamed: J5.14, R218.2
unnamed: J10.B28 (MIO35_PMU_GPO), TP43.1 (1_1)
unnamed: J10.B24 (PS_ERROR_OUT_M2C), TP12.1 (1_1)
unnamed: J10.B25 (PS_ERROR_STATUS_M2C), TP29.1 (1_1)
unnamed: J10.D24 (PWRGD_FPD_M2C), TP31.1 (1_1)
unnamed: J10.D25 (PWRGD_LPD_M2C), TP32.1 (1_1)
unnamed: J10.D26 (PWRGD_PL_M2C), TP33.1 (1_1)
unnamed: J11.13, R206.1
unnamed: J11.14, R207.1
unnamed: J11.19, R100.2
unnamed: J12.14, R67.1
unnamed: J14.1, R65.2
unnamed: LDO1.5 (ADJ), R61.1, R82.2
unnamed: LDO1.1 (EN), R59.2
unnamed: LDO3.5 (ADJ), R55.2, R83.1
unnamed: LDO3.1 (EN), R14.2
unnamed: LDO4.5 (ADJ), R103.2, R109.1
unnamed: LDO4.1 (EN), R85.2
unnamed: LDO7.5 (ADJ), R33.1, R104.2
unnamed: LDO7.1 (EN), R32.2
unnamed: LDO8.5 (ADJ), R36.1, R105.2
unnamed: LDO8.1 (EN), R35.2
unnamed: LDO9.5 (ADJ), R43.1, R106.2
unnamed: LDO9.1 (EN), R41.2
unnamed: LDO10.5 (ADJ), R40.1, R107.2
unnamed: LDO10.1 (EN), R38.2
unnamed: C148.2, FB2.1, MOSFET1.3 (D), U29.2 (ANODE)
unnamed: MOSFET1.1 (G), Q13.3 (D), R137.2
unnamed: C134.1, Q12.1 (G), R111.2, U27.14 (VCC)
unnamed: Q12.2 (S), R111.1, U27.7 (PG)
unnamed: C243.1, Q15.3 (D), R161.2, U17.42 (RESET_N)
unnamed: C250.1, Q20.3 (D), Q21.1 (G), R175.2
unnamed: Q21.3 (D), R214.2
unnamed: R22.1, R23.1, R24.1, R26.2
unnamed: R45.2, R55.1
unnamed: R60.2, R82.1
unnamed: R102.2, R103.1
unnamed: R34.2, R104.1
unnamed: R37.2, R105.1
unnamed: R42.2, R106.1
unnamed: R39.2, R107.1
unnamed: U1.5 (B1), U55.2 (DIN)
unnamed: U1.4 (B2), U55.4 (ROUT)
unnamed: TP19.1 (1_1), U2.10 (SDO)
unnamed: TP20.1 (1_1), U4.10 (SDO)
unnamed: R2.1, U5.2 (TRIM)
unnamed: C121.1, U6.10 (DV/DT)
unnamed: R58.1, U6.9 (EN)
unnamed: R68.2, U6.4 (ILIMIT)
unnamed: C122.1, R66.2, U6.5 (MODE)
unnamed: R87.1, U9.7 (USBDM)
unnamed: R31.1, U9.6 (USBDP)
unnamed: C107.1, J14.2, R87.2, U10.1 (CH1)
unnamed: C69.1, J14.3, R31.2, U10.2 (CH2)
unnamed: C245.1, R208.2, R209.1, U11.4 (FB)
unnamed: C103.1, C104.1, U13.7 (OUT), U13.8 (FEEDBACK), U15.6 (REF)
unnamed: R10.1, U14.2 (TRIM)
unnamed: TP15.1 (1_1), U15.10 (SDO)
unnamed: R162.1, U16.24 (RBIAS)
unnamed: R163.2, U16.22 (VBUS)
unnamed: C186.1, U16.20 (VDD33)
unnamed: R8.1, U17.52 (ATESET)
unnamed: R11.1, U17.56 (RBIAS)
unnamed: R12.1, U17.41 (SPI_CE_N/CFG_NON_REM)
unnamed: R13.1, U17.40 (SPI_DI/CFG_BC_EN)
unnamed: C181.2, U17.51 (USB3UP_RXDM)
unnamed: C182.2, U17.50 (USB3UP_RXDP)
unnamed: C183.2, U17.48 (USB3UP_TXDM)
unnamed: C184.2, U17.47 (USB3UP_TXDP)
unnamed: C130.1, U6.8 (GATE), U26.4 (G)
unnamed: U6.6 (SOURCE), U6.7 (SOURCE), U26.1 (S), U26.2 (S), U26.3 (S)
unnamed: R130.1, U27.2 (BST)
unnamed: R110.1, U27.3 (EN)
unnamed: R132.2, U27.4 (FB)
unnamed: C136.1, U27.6 (SS)
unnamed: C135.2, C137.2, L1.1, U27.16 (SW)
unnamed: C144.2, R135.2, R136.1, U28.4 (FB)
unnamed: R143.2, R144.1, U32.10 (FB)
unnamed: R147.2, R148.1, U34.17 (FB)
unnamed: R151.2, R152.1, U35.17 (FB)
unnamed: R157.2, R158.1, U37.17 (FB)
unnamed: C180.1, R29.2, U43.7 (VREF2), U43.8 (EN)
unnamed: R176.1, R210.2, U45.7 (*WC)
unnamed: C169.1, R153.2, R154.1, U50.4 (FB)
unnamed: C196.1, R155.2, R177.1, U51.4 (FB)
unnamed: C225.2, U52.12 (TRCT0)
unnamed: C226.2, U52.6 (TRCT1)
unnamed: C227.2, U52.1 (TRCT2)
unnamed: C228.2, U52.7 (TRCT3)
unnamed: R201.2, U53.44 (INT_PWDN)
unnamed: R182.2, U53.20 (JTAG_CLK)
unnamed: R181.2, U53.23 (JTAG_TDI)
unnamed: R183.2, U53.22 (JTAG_TMS)
unnamed: R184.1, U53.12 (RBIAS)
unnamed: C223.1, C224.2, U53.15 (X_I)
unnamed: U54.5 (B1), U55.1 (DE), U55.8 (*RE)
unnamed: R27.1, U54.4 (B2)
unnamed: C49.1, R22.2, U55.10 (RIN+), U55.12 (DOUT+)
unnamed: C50.1, R23.2, U55.9 (RIN-), U55.11 (DOUT-)
unnamed: R74.2, U56.4 (EN)
unnamed: R76.2, U56.3 (FAULT)
unnamed: R112.2, SW3.3 (B), SW3.4 (B), U58.4 (*MR)
unnamed: C106.1, U58.3 (CT)
unnamed: C61.1, U59.3 (CT)
OUTCLK: J2.35, J10.D16 (HDA00_CC)
OscClkOut: J3.B49 (HDB16_CC), J4.59
P5_ReadClk: J2.52, J10.C22 (HDA18)
P5_rst: J2.20, J10.D17 (HDA01)
PICO: J2.28, J10.D21 (HDA13)
PL_1V8: C88.1, C245.2, C246.2, J3.A44 (VCCO_HPB), J3.B42 (VCCO_HPB), J3.C44 (VCCO_HPC), J3.D42 (VCCO_HPC), J3.D59 (VCCO_HDC), J3.D60 (VCCO_HDC), J10.D01 (VCCO_HPA), J10.D02 (VCCO_HPA), R18.1, R19.1, R20.1, R21.1, R208.1, U11.1 (OUT)
PL_2V5: C85.1, C157.2, C158.2, J3.B59 (VCCO_HDB), J3.B60 (VCCO_HDB), J10.B13 (VCCO_HDA), J10.B14 (VCCO_HDA), R86.2, R108.2, R143.1, U32.5 (OUT), U32.6 (OUT), U32.12 (OUT_S)
POCI: J2.26, J10.D22 (HDA14)
PS_1V2: C163.2, C164.2, R147.1, U17.5 (VDD12), U17.12 (VDD12), U17.15 (VDD12), U17.21 (VDD12), U17.28 (VDD12), U17.33 (VDD12), U17.43 (VDD12), U17.49 (VDD12), U34.12 (VOUT), U34.13 (VOUT), U34.14 (VOUT), U34.15 (VOUT), U34.16 (VOS)
PS_1V8: C5.1, C21.1, C65.1, C166.2, C167.2, C178.1, C199.1, C200.1, C201.1, C202.1, C203.1, C204.1, C205.1, C206.1, C241.1, C242.1, IC1.23 (VDDO3), J5.18, J5.20, J12.2, Q15.1 (G), Q20.1 (G), R81.2, R151.1, R164.1, R181.1, R182.1, R183.1, R185.1, R186.1, R187.1, R188.1, R189.1, R190.1, R191.1, R192.1, R201.1, R202.1, R204.1, U1.7 (VCCA), U1.10 (DIR1), U9.1 (VCCIO), U16.8 (REFSEL0), U16.11 (REFSEL1), U16.14 (REFSEL2), U16.28 (VDD18), U16.30 (VDD18), U16.32 (VDDIO), U35.12 (VOUT), U35.13 (VOUT), U35.14 (VOUT), U35.15 (VOUT), U35.16 (VOS), U43.2 (VREF1), U53.19 (VDDIO), U53.30 (VDDIO), U53.41 (VDDIO), U54.7 (VCCA), U54.10 (DIR1)
PS_3V3: C17.1, C46.1, C48.1, C51.2, C53.2, C54.2, C66.1, C67.1, C68.1, C72.1, C168.2, C172.2, C173.2, C179.1, C194.1, C195.2, C233.1, C234.1, C235.1, C236.1, C237.1, C238.1, C239.1, C240.1, C249.1, IC1.13 (VDDO0), IC1.16 (VDDO1), IC1.25 (VDDO4), IC1.32 (VDDO5), J5.11, J5.13, R26.1, R29.1, R44.1, R74.1, R76.1, R84.2, R101.1, R115.2, R157.1, R159.1, R160.1, R161.1, R175.1, R176.2, R179.1, R213.1, R222.2, U1.6 (VCCB), U9.8 (3V3OUT), U9.10 (VCC), U12.2, U17.16 (VDD33), U17.31 (VDD33), U17.37 (VBUS_DET), U17.44 (VDD33), U17.55 (VDD33), U37.12 (VOUT), U37.13 (VOUT), U37.14 (VOUT), U37.15 (VOUT), U37.16 (VOS), U45.1 (E0), U45.8 (VCC), U50.8 (IN), U51.8 (IN), U52.14 (RIGHT_YLW_AN), U52.16 (LEFT_GRNORG_AN), U54.6 (VCCB), U55.14 (VCC), U56.5 (IN), U57.13 (VCC), U57.15 (VCC)
PS_3V3_PGOOD: R178.2, U36.1 (A1), U36.3 (A2), U37.2 (PG)
PS_POR: J10.C15 (PS_POR_L), Q15.2 (S), Q20.2 (S), R204.2, TP41.1 (1_1), U16.27 (RESETB), U53.43 (RESET_N), U59.6 (*RESET)
PS_SRST: J10.C16 (PS_SRST_C2M_L), R67.2, TP42.1 (1_1), U58.6 (*RESET)
PWROFF_C2M_B: C60.1, J8.3, J10.B26 (PWROFF_C2M_L), Q12.3 (D), TP37.1 (1_1), U28.3 (PG)
Psec5TriggerOut: J2.50, J10.D18 (HDA02)
READBIAS1: J2.07, U4.4 (VOUTC)
READBIAS2: J2.05, U4.5 (VOUTD)
REFCLK: J3.C48 (HDB08_CC), J4.13
SD_VDD: J5.15, J5.17, J5.19, R221.2, R222.1
SIGNAL1+: J2.06, R9.1
SIGNAL1-: J2.08, R15.1
SIGNAL2+: J2.14, R16.1
SIGNAL2-: J2.16, R17.1
SIGNAL3+: J2.22, R25.1
SIGNAL3-: J2.24, R30.1
SIGNAL4+: J2.30, R46.1
SIGNAL4-: J2.32, R47.1
SIGNAL5+: J2.46, R48.1
SIGNAL5-: J2.48, R49.1
SIGNAL6+: J2.54, R50.1
SIGNAL6-: J2.56, R51.1
SIGNAL7+: J2.62, R52.1
SIGNAL7-: J2.64, R53.1
SIGNAL8+: J2.70, R54.1
SIGNAL8-: J2.72, R72.1
SPIclk: J2.18, J10.C20 (HDA08_CC)
SYNC_N: J3.A52 (HDB23), J4.17
TRIGGERIN: J2.78, J10.D20 (HDA12)
USB_HUB_CLK_IN: IC1.14 (OUT1B), R115.1, R203.1, U17.54 (XTALI/CLK_IN)
USB_HUB_SMCLK: R145.2, R160.2, U17.38 (SPI_CLK/SMCLK)
USB_HUB_SMDAT: R146.2, R159.2, U17.39 (SPI_DO/SMDAT)
USB_PHY_REFCLK: IC1.22 (OUT3), U16.26 (REFCLK)
UTIL_3V3: C118.1, C119.1, C144.1, C145.1, C155.1, C229.1, C230.1, C231.1, C232.1, IC1.1 (VDD_DIG), IC1.4 (VDD_XTAL), IC1.7 (VDDA), R112.1, R113.1, R135.1, R137.1, TP35.1 (1_1), U28.1 (OUT), U58.1 (VDD), U58.2 (SENSE)
VCCOEN_PL_M2C: J10.A20 (VCCOEN_PL_M2C), U11.5 (EN), U32.9 (EN)
VCCOEN_PS_M2C: J10.A19 (VCCOEN_PS_M2C), U34.1 (EN), U35.1 (EN), U37.1 (EN)
VDD_BUCK_2V7: C12.2, C13.1, C14.2, LDO1.2 (IN), LDO9.2 (IN), LDO10.2 (IN), R38.1, R41.1, R59.1, U5.1 (+VOUT)
VDD_BUCK_4V: C8.2, C10.2, C15.2, C94.2, LDO3.2 (IN), LDO4.2 (IN), LDO7.2 (IN), LDO8.2 (IN), R14.1, R32.1, R35.1, R85.1, U14.1 (+VOUT)
V_ped1: J4.55, U15.12 (VOUTE)
V_ped2: J4.53, U15.13 (VOUTF)
V_ped3: J4.51, U15.14 (VOUTG)
V_ped4: J4.49, U15.15 (VOUTH)
V_ped5: J4.47, U15.2 (VOUTA)
V_ped6: J4.45, U15.3 (VOUTB)
V_ped7: J4.43, U15.4 (VOUTC)
V_ped8: J4.41, U15.5 (VOUTD)
WBUFBIAS: J2.11, U4.3 (VOUTB)
